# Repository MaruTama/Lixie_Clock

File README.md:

# Lixie Clock
What is the Lixie ?  
Lixie is a display unit using acrylic board like Nixie Tube.

# Other
表示器のグリッドは0.05mmで作成している

# Using libraries
[kicad_ArduinoNano](https://github.com/kiwichrish/kicad_ArduinoNano)
https://forum.kicad.info/t/where-are-the-momentary-bush-button-switches-located/5695
[Tiny_RTC](https://www.elecrow.com/wiki/index.php?title=Tiny_RTC)
[DateTime](http://playground.arduino.cc/Code/DateTime)

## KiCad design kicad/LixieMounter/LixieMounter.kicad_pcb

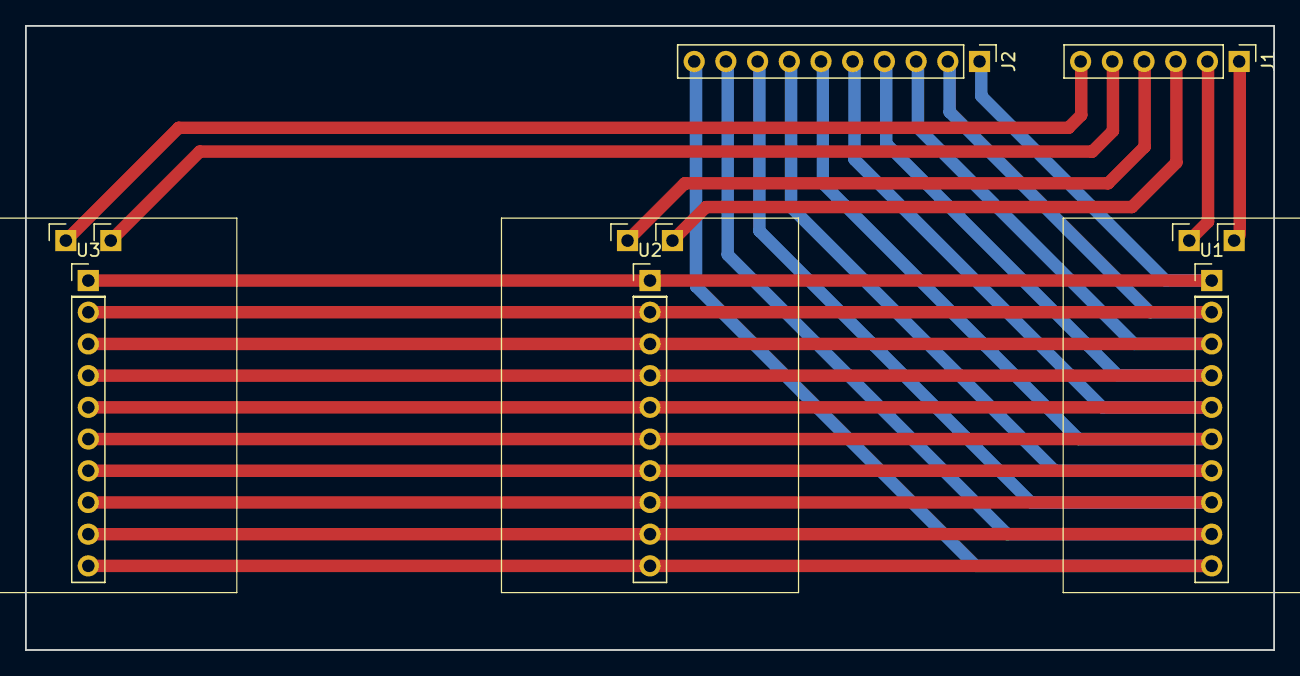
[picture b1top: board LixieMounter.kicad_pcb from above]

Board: 2 copper layers, 100.0 x 50.0 mm, 5 parts (0 on the bottom side), 16 nets.

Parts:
J1: Conn_01x06; Socket_Strip_Straight_1x06_Pitch2.54mm
J2: Conn_01x10; Socket_Strip_Straight_1x10_Pitch2.54mm
U1, U2, U3: 2DigitLixie; LixieUnit

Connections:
unnamed: J1.1, U1.1
unnamed: J1.2, U1.2
unnamed: J1.3, U2.1
unnamed: J1.4, U2.2
unnamed: J1.5, U3.1
unnamed: J1.6, U3.2
unnamed: J2.1, U1.3, U2.3, U3.3
unnamed: J2.2, U1.4, U2.4, U3.4
unnamed: J2.3, U1.5, U2.5, U3.5
unnamed: J2.4, U1.6, U2.6, U3.6
unnamed: J2.5, U1.7, U2.7, U3.7
unnamed: J2.6, U1.8, U2.8, U3.8
unnamed: J2.7, U1.9, U2.9, U3.9
unnamed: J2.8, U1.10, U2.10, U3.10
unnamed: J2.9, U1.11, U2.11, U3.11
unnamed: J2.10, U1.12, U2.12, U3.12

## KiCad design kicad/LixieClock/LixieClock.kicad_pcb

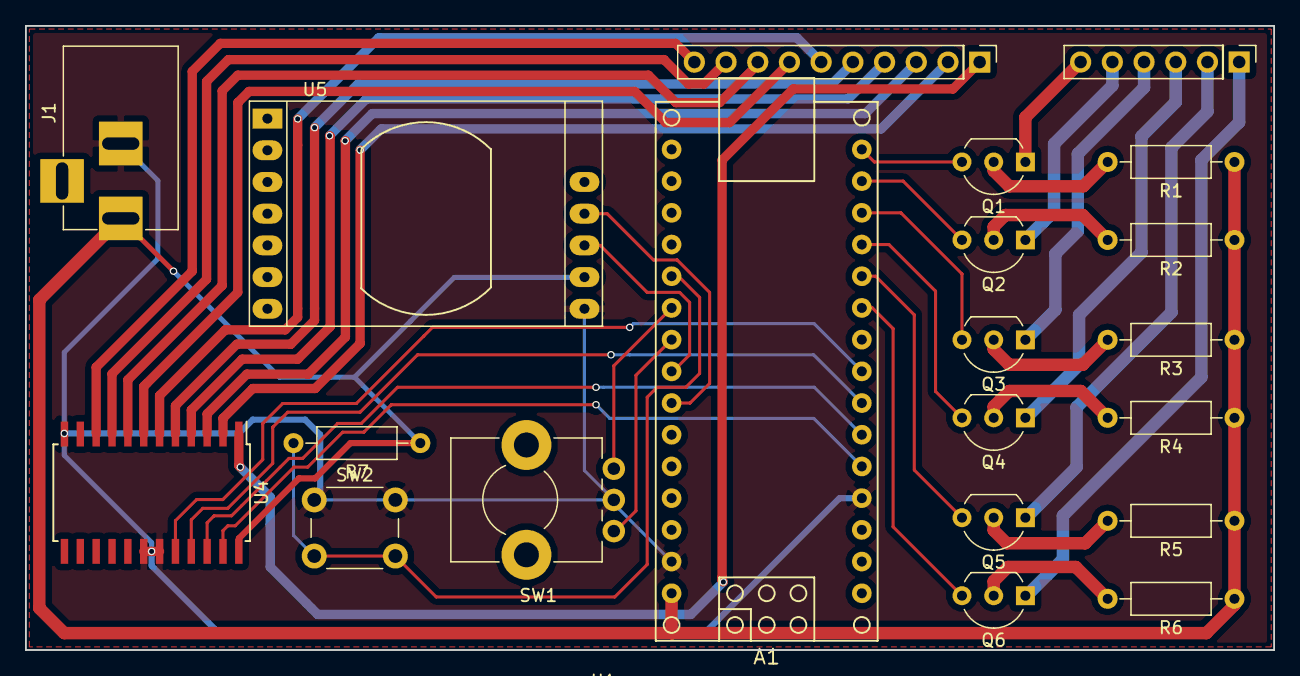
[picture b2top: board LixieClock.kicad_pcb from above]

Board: 2 copper layers, 100.0 x 50.0 mm, 20 parts (0 on the bottom side), 39 nets.

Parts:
A1: Arduino_Nano; arduino_nano
J1: Jack-DC; BARREL_JACK
Q1, Q2, Q3, Q4, Q5, Q6: Q_PNP_ECB; TO-92_Inline_Wide
R1, R2, R3, R4, R5, R6, R7: R; R_Axial_DIN0207_L6.3mm_D2.5mm_P10.16mm_Horizontal
SW1: Rotary_Encoder; Potentiometer_Alps_RK09K_Horizontal
SW2: SW_Push; SW_PUSH_6mm_h7.3mm
U1: 6DigitLixie
U4: 74HC154; SOIC-24W_7.5x15.4mm_Pitch1.27mm
U5: DS1307; DS1307_Socket_LongPads

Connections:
5V: A1.30, J1.1, R1.1, R2.1, R3.1, R4.1, R5.1, R6.1, R7.1, U4.24, U5.9
A0: A1.5, U4.23
A1: A1.6, U4.22
A2: A1.7, U4.21
A3: A1.8, U4.20
DGT0: A1.10, Q6.3
DGT1: A1.11, Q5.3
DGT2: A1.12, Q4.3
DGT3: A1.13, Q3.3
DGT4: A1.14, Q2.3
DGT5: A1.15, Q1.3
GND: A1.4, A1.29, J1.2, SW1.2, SW2.1, U4.12, U4.18, U4.19, U5.8
unnamed: A1.21, SW1.1
unnamed: A1.22, SW1.3
unnamed: Q1.1, U1.6
unnamed: Q1.2, R1.2
unnamed: Q2.1, U1.5
unnamed: Q2.2, R2.2
unnamed: Q3.1, U1.4
unnamed: Q3.2, R3.2
unnamed: Q4.1, U1.3
unnamed: Q4.2, R4.2
unnamed: Q5.1, U1.2
unnamed: Q5.2, R5.2
unnamed: Q6.1, U1.1
unnamed: Q6.2, R6.2
unnamed: U1.7, U4.1
unnamed: U1.8, U4.2
unnamed: U1.9, U4.3
unnamed: U1.10, U4.4
unnamed: U1.11, U4.5
unnamed: U1.12, U4.6
unnamed: U1.13, U4.7
unnamed: U1.14, U4.8
unnamed: U1.15, U4.9
unnamed: U1.16, U4.10
SCL: A1.24, U5.11
SDA: A1.23, U5.10
SW: A1.20, R7.2, SW2.2

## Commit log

2018-07-15 Create LICENSE
2018-07-15 表示機のパターンを引き終えた
2018-07-16 回路図のコンポーネントを作成、配置した。
2018-07-16 面付け基板にした。また、面付けの場合、配線が恥から0.4mm以上離れてなければならないので離した。
2018-07-16 時計の回路を書き終えた
2018-07-16 PCB上のフットプリントのコンポーネントを作成し、配置した。
2018-07-18 100×100mmのサイズに収めるにはちょっと無理があったので、LixieUnit <-> Mounter <-> MainBoardという3層構造に変更した。
2018-07-18 自動配線後、手作業で引き直し中
2018-07-18 暫定的な基板の完成
2018-08-02 ロータリーエンコーダが使えるようになった。
2018-08-02 タクトスイッチの入力を検出できるようになった。チャタリングへの対応も行った。
2018-08-02 RTCが使えることを確認した
2018-08-03 LEDの表示制御と時間設定が行えるようになった
